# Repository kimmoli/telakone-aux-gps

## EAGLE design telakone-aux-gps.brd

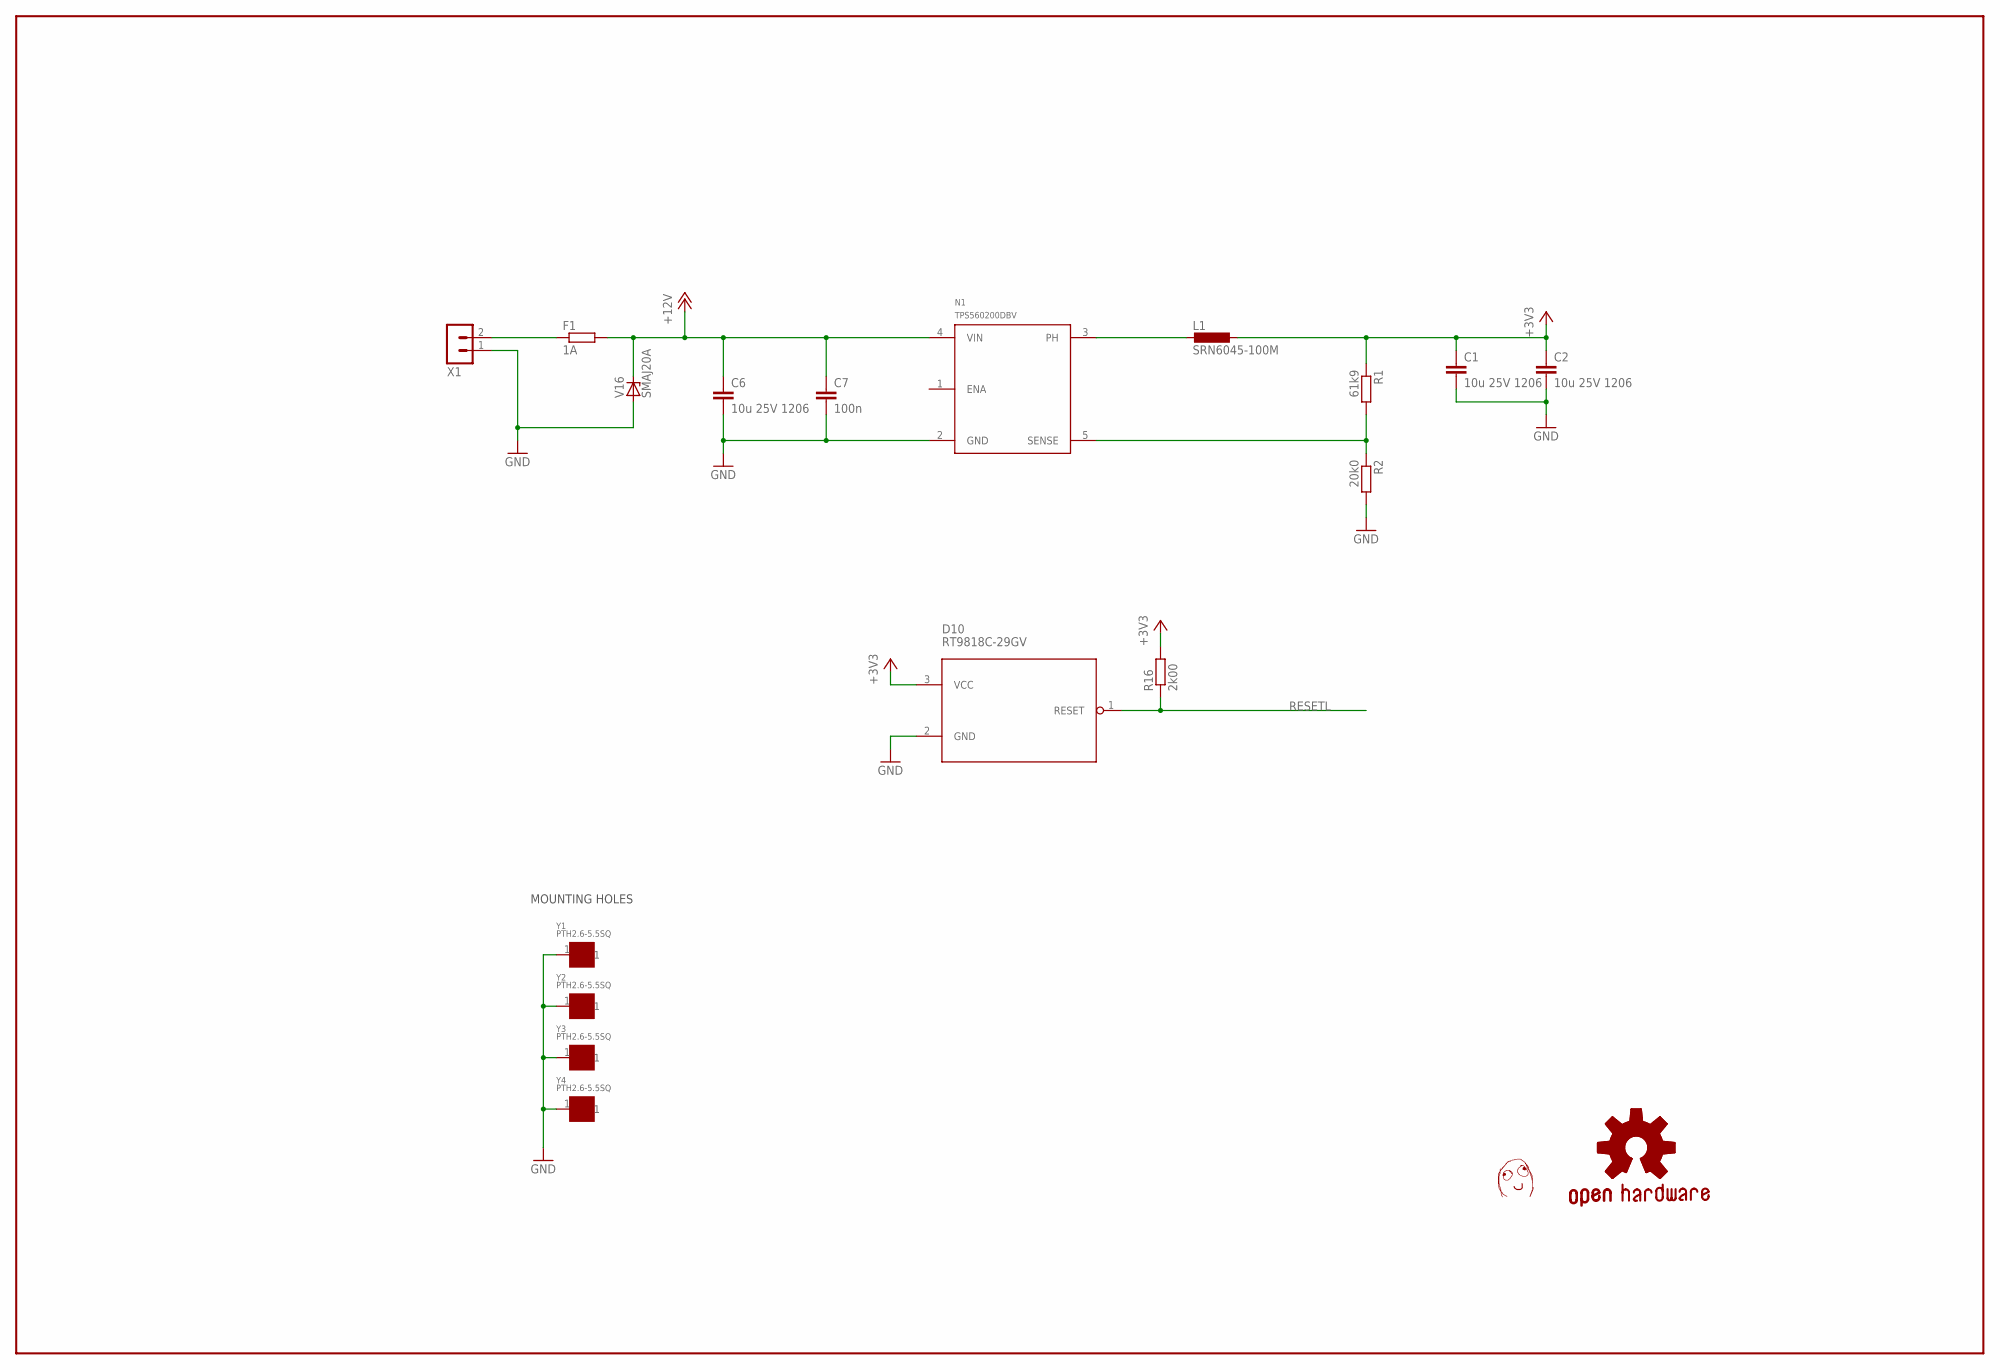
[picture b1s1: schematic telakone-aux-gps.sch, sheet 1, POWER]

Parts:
C1, C2, C6: 10u 25V 1206; C1206
C7: 100n; C0603
D10: RT9818C-29GV; SOT23
F1: 1A; R1206
L1: SRN6045-100M; SRN6045
N1: TPS560200DBV; SOT95P280X145-5N
R1: 61k9; R0603
R2: 20k0; R0603
R16: 2k00; R0603
U$5: DAFUG
V16: SMAJ20A; DO214AC
X1: TE_RUUVILIITIN2
Y1, Y2, Y3, Y4: PTH2.6-5.5SQ; PTH-2.6-5.5SQ

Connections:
+3V3: C1.1, C2.1, D10.3 (VCC), L1.1, R1.1, R16.2; also elsewhere on the board
+12V: C6.1, C7.1, F1.2, N1.4 (VIN), V16.C; also elsewhere on the board
+12V_IN: F1.1, X1.2
GND: C1.2, C2.2, C6.2, C7.2, D10.2 (GND), N1.2 (GND), R2.2, V16.A, X1.1, Y1.1, Y2.1, Y3.1, Y4.1; also elsewhere on the board
N1_PHASE: L1.2, N1.3 (PH)
N1_SENSE: N1.5 (SENSE), R1.2, R2.1
RESETL: D10.1 (RESET), R16.1; also elsewhere on the board

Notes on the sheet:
MOUNTING HOLES

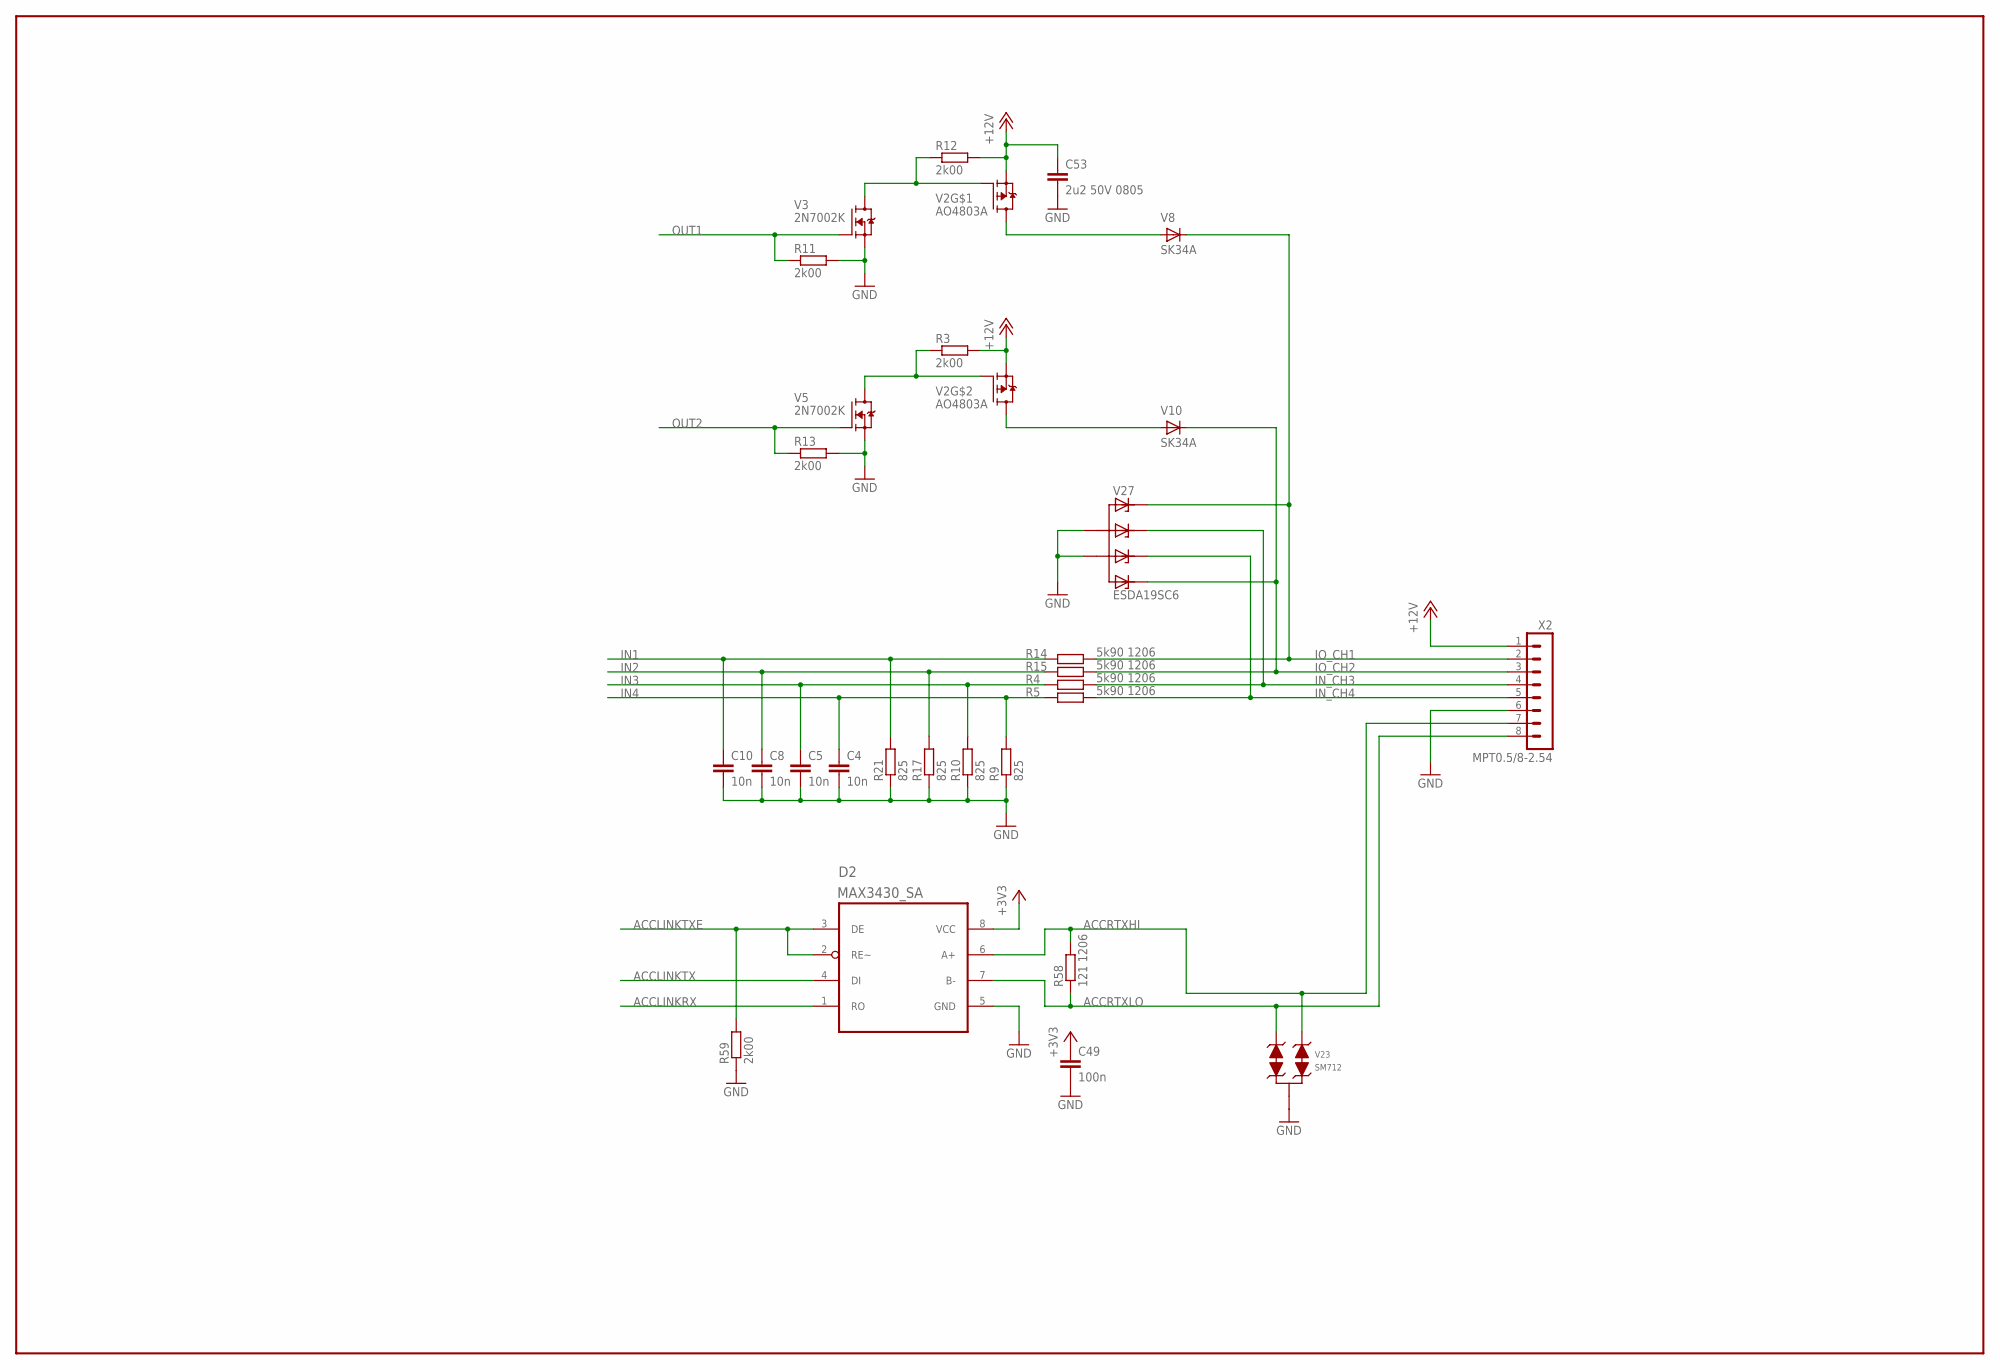
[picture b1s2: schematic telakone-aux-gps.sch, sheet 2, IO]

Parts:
C4, C5, C8, C10: 10n; C0603
C49: 100n; C0603
C53: 2u2 50V 0805; C0805
D2: MAX3430_SA; SOIC8-N_MC
R3, R11, R12, R13, R59: 2k00; R0603
R4, R5, R14, R15: 5k90 1206; R1206
R9, R10, R17, R21: 825; R0603
R58: 121 1206; R1206
V2: AO4803A; SOIC8-N_MC
V3, V5: 2N7002K; SOT23
V8, V10: SK34A; DO214AC
V23: SM712; SOT23
V27: ESDA19SC6; SOT23-6
X2: MPT0.5/8-2.54

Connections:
+3V3: C49.1, D2.8 (VCC); also elsewhere on the board
+12V: C53.1, R3.2, R12.2, V2.1 (S), V2.3 (S), X2.1; also elsewhere on the board
ACCLINKRX: D2.1 (RO); also elsewhere on the board
ACCLINKTX: D2.4 (DI); also elsewhere on the board
ACCLINKTXE: D2.2 (RE~), D2.3 (DE), R59.2; also elsewhere on the board
ACCRTXHI: D2.6 (A+), R58.2, V23.1, X2.7
ACCRTXLO: D2.7 (B-), R58.1, V23.2, X2.8
GND: C4.2, C5.2, C8.2, C10.2, C49.2, C53.2, D2.5 (GND), R9.1, R10.1, R11.2, R13.2, R17.1, R21.1, R59.1, V3.2 (S), V5.2 (S), V23.3, V27.2 (A), V27.5 (A1), X2.6; also elsewhere on the board
IN1: C10.1, R14.1, R21.2; also elsewhere on the board
IN2: C8.1, R15.1, R17.2; also elsewhere on the board
IN3: C5.1, R4.1, R10.2; also elsewhere on the board
IN4: C4.1, R5.1, R9.2; also elsewhere on the board
IN_CH3: R4.2, V27.3 (C1), X2.4
IN_CH4: R5.2, V27.4 (C2), X2.5
IO_CH1: R14.2, V8.C, V27.1 (C), X2.2
IO_CH2: R15.2, V10.C, V27.6 (C3), X2.3
unnamed: R3.1, V2.2 (G), V5.3 (D)
unnamed: R12.1, V2.4 (G), V3.3 (D)
NERT: V2.5 (D), V2.6 (D), V8.A
NERT1: V2.7 (D), V2.8 (D), V10.A
OUT1: R11.1, V3.1 (G); also elsewhere on the board
OUT2: R13.1, V5.1 (G); also elsewhere on the board

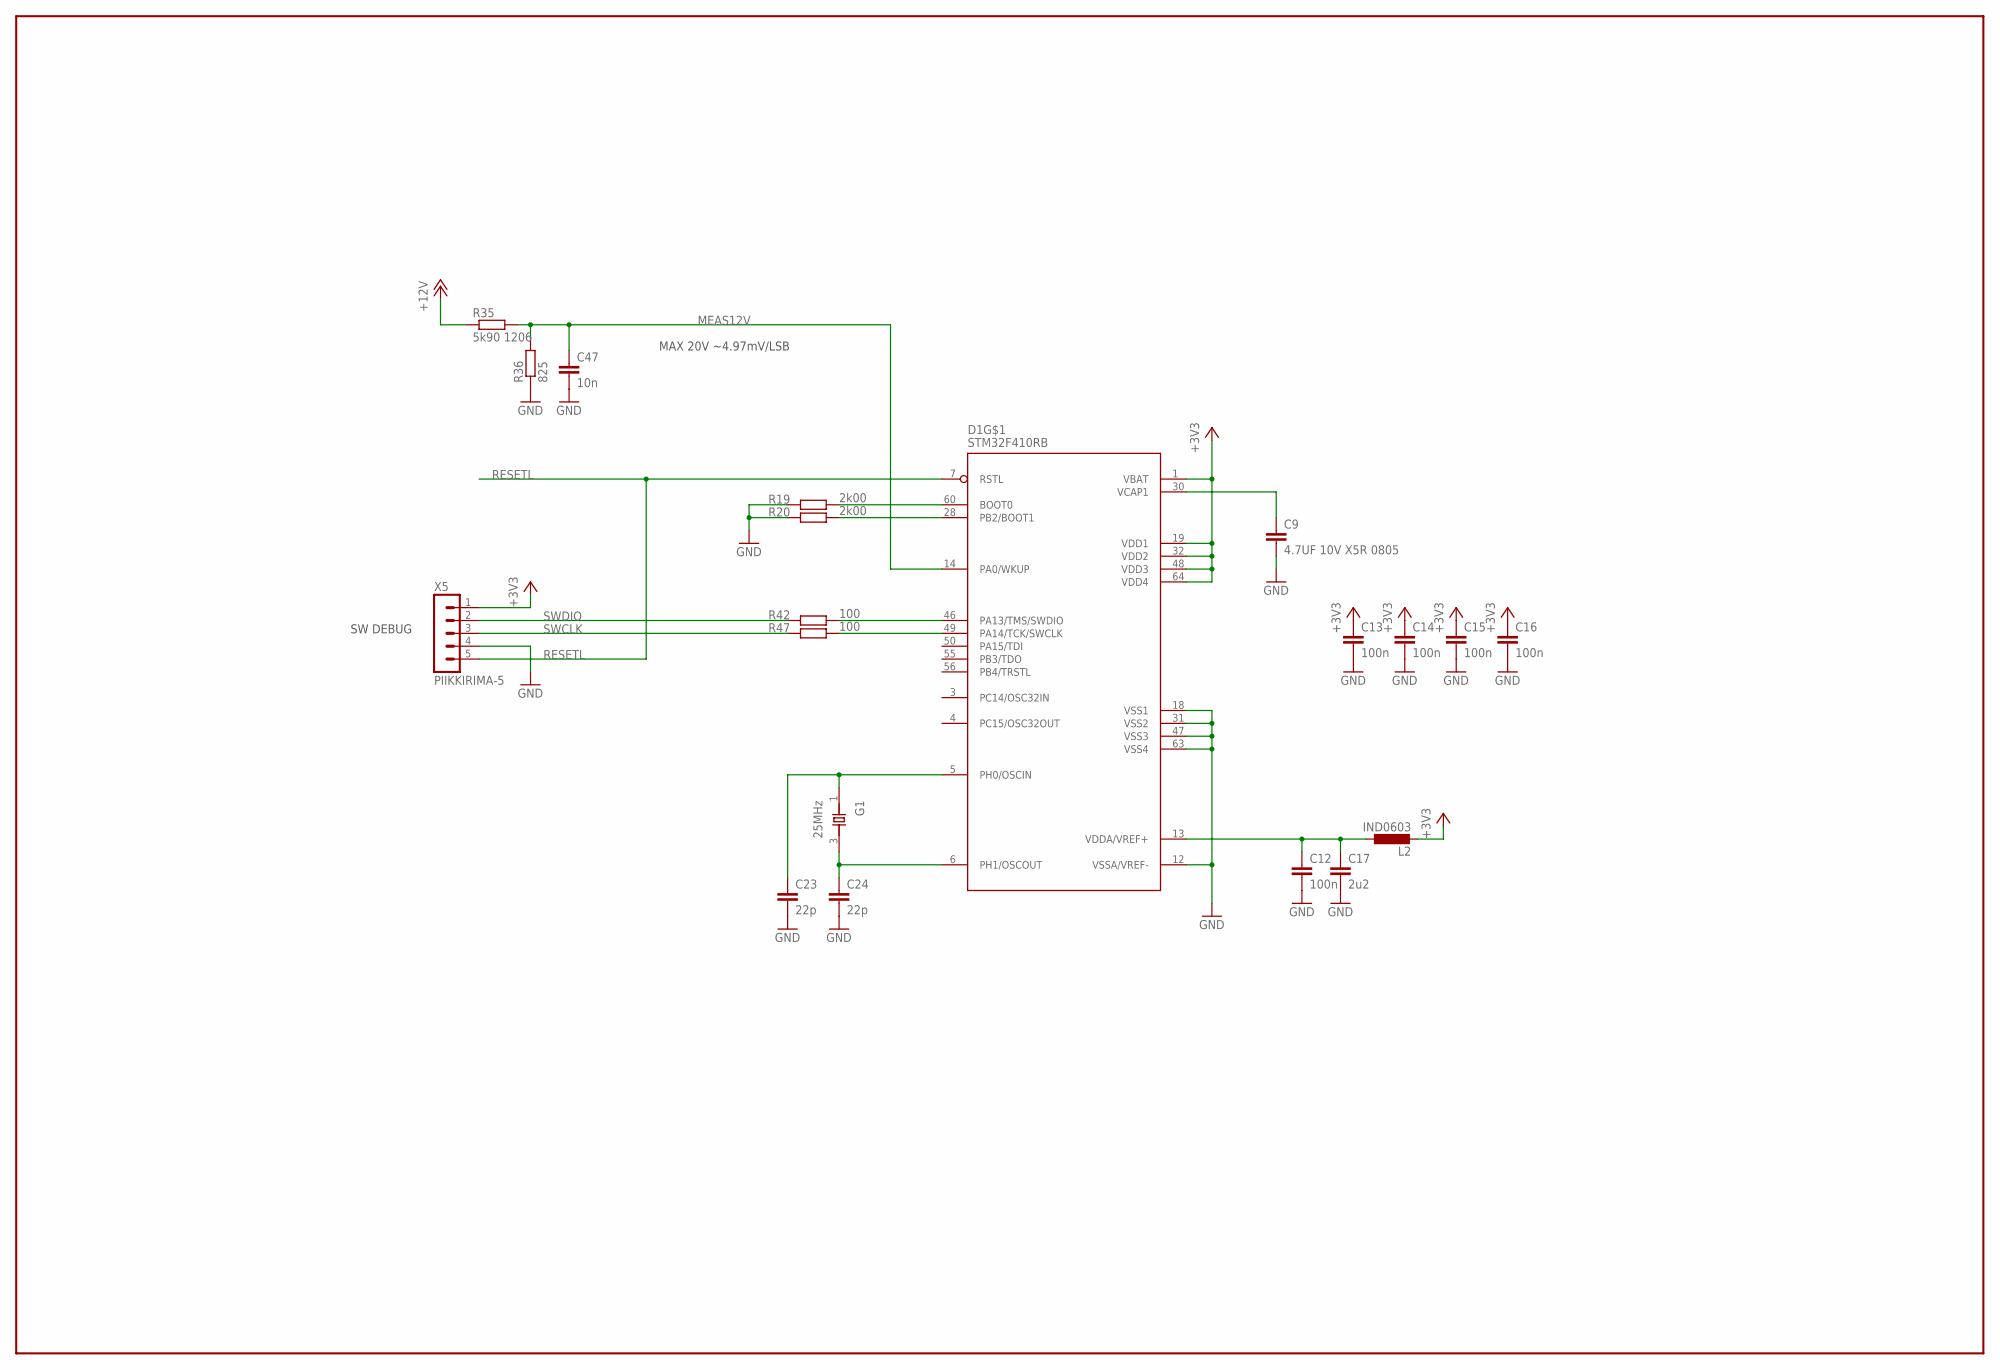
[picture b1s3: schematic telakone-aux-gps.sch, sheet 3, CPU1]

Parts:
C9: 4.7UF 10V X5R 0805; C0805
C12, C13, C14, C15, C16: 100n; C0603
C17: 2u2; C0603
C23, C24: 22p; C0603
C47: 10n; C0603
D1: STM32F410RB; LQFP-64
G1: 25MHz; X_3225
L2: IND0603; R0603
R19, R20: 2k00; R0603
R35: 5k90 1206; R1206
R36: 825; R0603
R42, R47: 100; R0603
X5: PIIKKIRIMA-5

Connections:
+3V3: C13.1, C14.1, C15.1, C16.1, D1.1 (VBAT), D1.19 (VDD1), D1.32 (VDD2), D1.48 (VDD3), D1.64 (VDD4), L2.2, X5.1; also elsewhere on the board
+12V: R35.1; also elsewhere on the board
BOOT0: D1.60 (BOOT0), R19.2
BOOT1: D1.28 (PB2/BOOT1), R20.2
GND: C9.2, C12.2, C13.2, C14.2, C15.2, C16.2, C17.2, C23.2, C24.2, C47.2, D1.12 (VSSA/VREF-), D1.18 (VSS1), D1.31 (VSS2), D1.47 (VSS3), D1.63 (VSS4), R19.1, R20.1, R36.1, X5.4; also elsewhere on the board
MEAS12V: C47.1, D1.14 (PA0/WKUP), R35.2, R36.2
OSCIN: C23.1, D1.5 (PH0/OSCIN), G1.1 (X1)
OSCOUT: C24.1, D1.6 (PH1/OSCOUT), G1.3 (X2)
RESETL: D1.7 (RSTL), X5.5; also elsewhere on the board
SWCLK: R47.1, X5.3
SWCLK_CPU: D1.49 (PA14/TCK/SWCLK), R47.2
SWDIO: R42.1, X5.2
SWDIO_CPU: D1.46 (PA13/TMS/SWDIO), R42.2
VCAP1: C9.1, D1.30 (VCAP1)
VDDA: C12.1, C17.1, D1.13 (VDDA/VREF+), L2.1

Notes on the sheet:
SW DEBUG
MAX 20V ~4.97mV/LSB

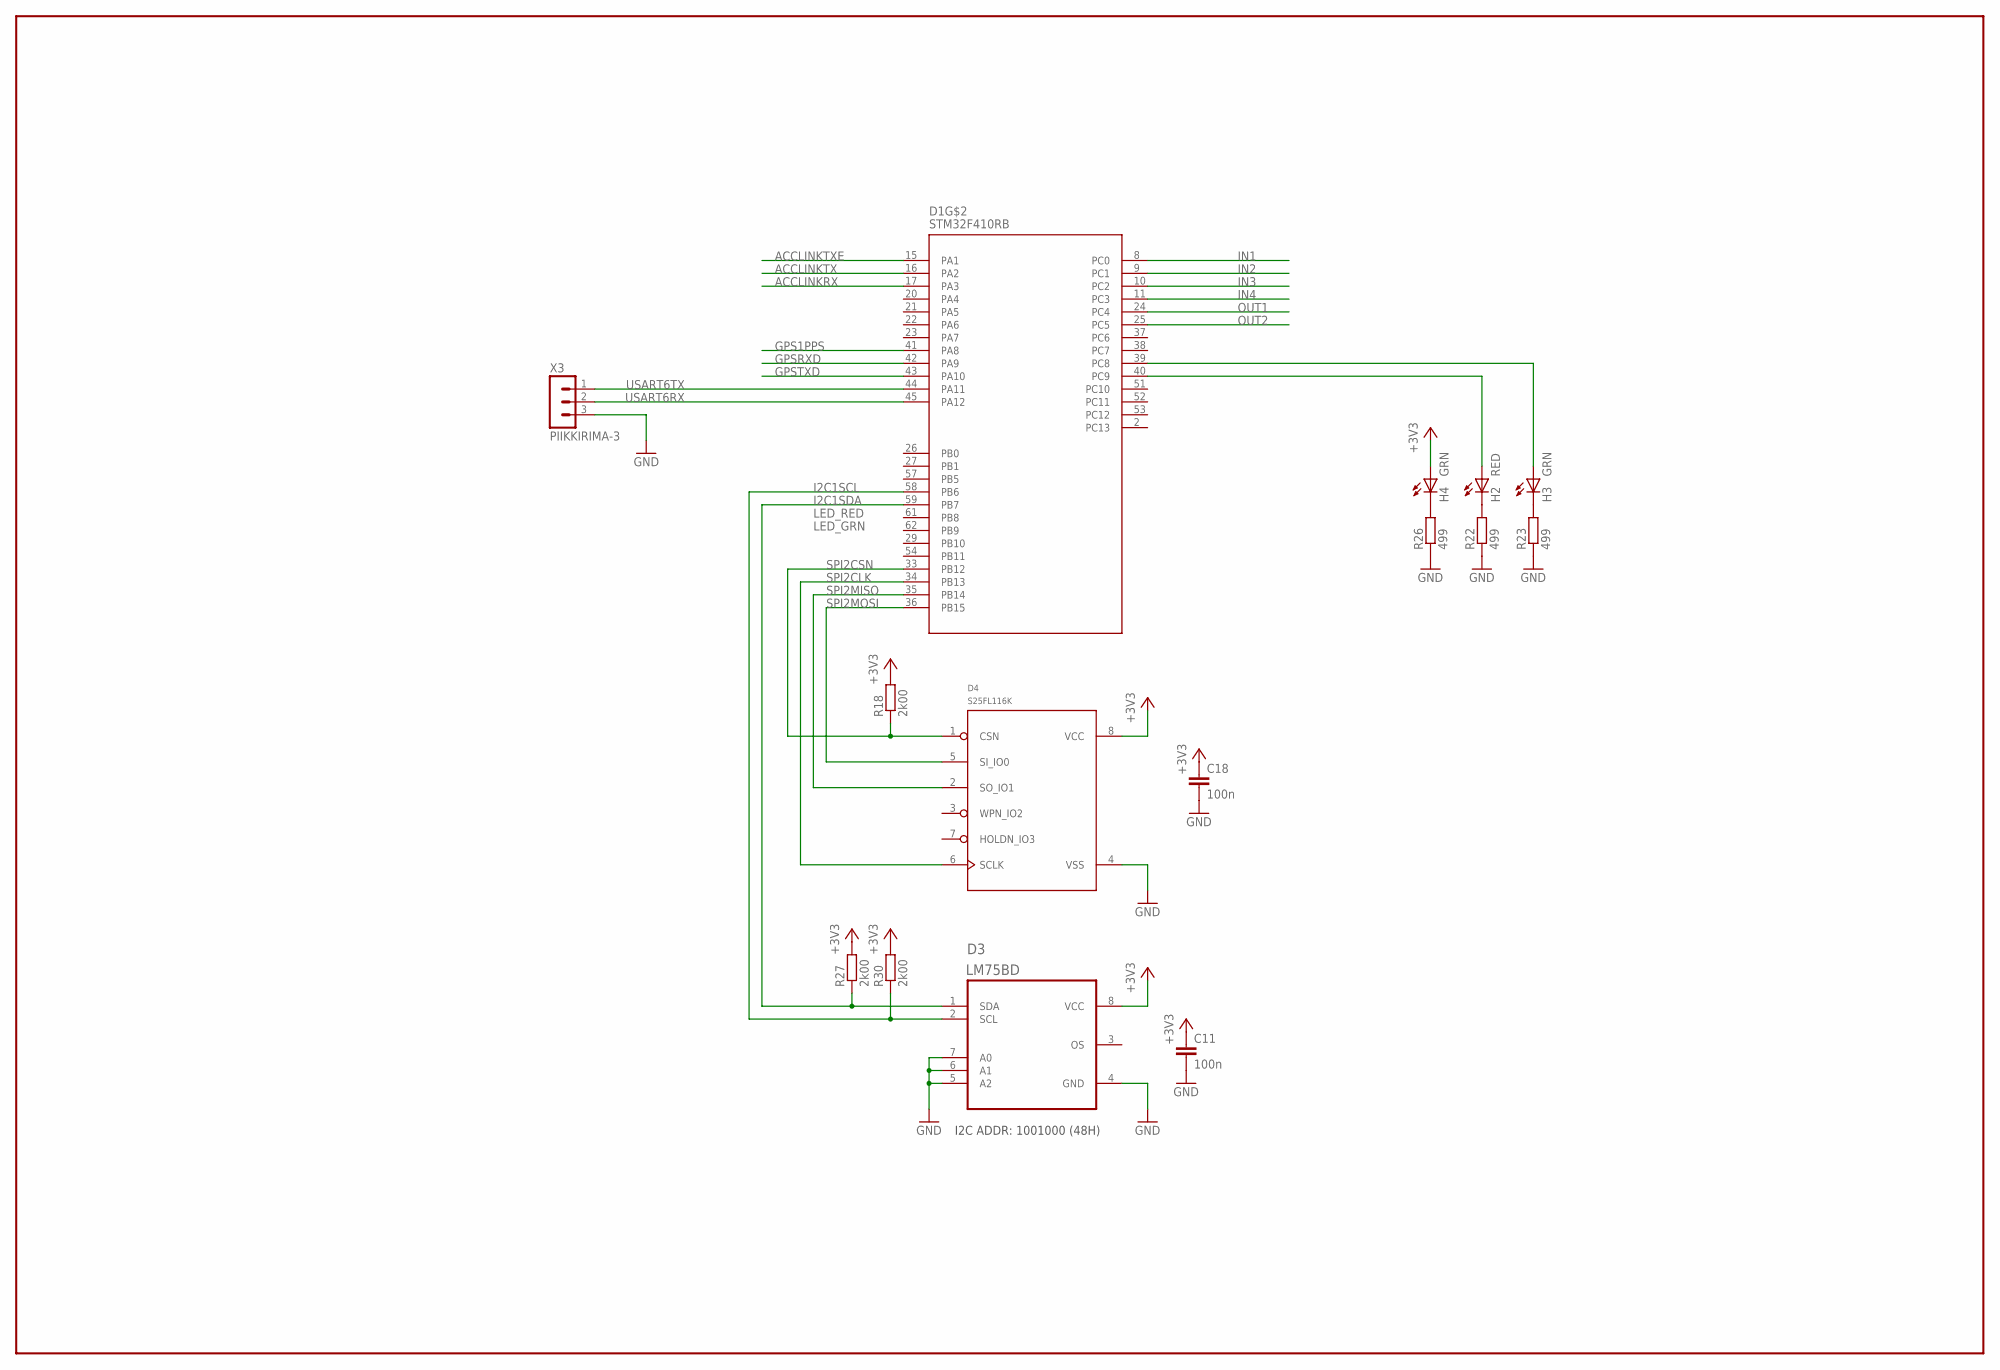
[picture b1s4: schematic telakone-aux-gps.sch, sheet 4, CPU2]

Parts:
C11, C18: 100n; C0603
D1: STM32F410RB; LQFP-64
D3: LM75BD; SOIC8-N_MC
D4: S25FL116K; SOIC8-N_MC
H2: RED; CHIP-LED0603
H3, H4: GRN; CHIP-LED0603
R18, R27, R30: 2k00; R0603
R22, R23, R26: 499; R0603
X3: PIIKKIRIMA-3

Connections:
+3V3: C11.1, C18.1, D3.8 (VCC), D4.8 (VCC), H4.A, R18.2, R27.2, R30.2; also elsewhere on the board
ACCLINKRX: D1.17 (PA3); also elsewhere on the board
ACCLINKTX: D1.16 (PA2); also elsewhere on the board
ACCLINKTXE: D1.15 (PA1); also elsewhere on the board
GND: C11.2, C18.2, D3.4 (GND), D3.5 (A2), D3.6 (A1), D3.7 (A0), D4.4 (VSS), R22.1, R23.1, R26.1, X3.3; also elsewhere on the board
GPS1PPS: D1.41 (PA8); also elsewhere on the board
GPSRXD: D1.42 (PA9); also elsewhere on the board
GPSTXD: D1.43 (PA10); also elsewhere on the board
I2C1SCL: D1.58 (PB6), D3.2 (SCL), R30.1
I2C1SDA: D1.59 (PB7), D3.1 (SDA), R27.1
IN1: D1.8 (PC0); also elsewhere on the board
IN2: D1.9 (PC1); also elsewhere on the board
IN3: D1.10 (PC2); also elsewhere on the board
IN4: D1.11 (PC3); also elsewhere on the board
LED_GRN: D1.39 (PC8), H3.A
LED_RED: D1.40 (PC9), H2.A
unnamed: H3.C, R23.2
unnamed: H2.C, R22.2
unnamed: H4.C, R26.2
OUT1: D1.24 (PC4); also elsewhere on the board
OUT2: D1.25 (PC5); also elsewhere on the board
SPI2CLK: D1.34 (PB13), D4.6 (SCLK)
SPI2CSN: D1.33 (PB12), D4.1 (CSN), R18.1
SPI2MISO: D1.35 (PB14), D4.2 (SO_IO1)
SPI2MOSI: D1.36 (PB15), D4.5 (SI_IO0)
USART6RX: D1.45 (PA12), X3.2
USART6TX: D1.44 (PA11), X3.1

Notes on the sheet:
I2C ADDR: 1001000 (48H)

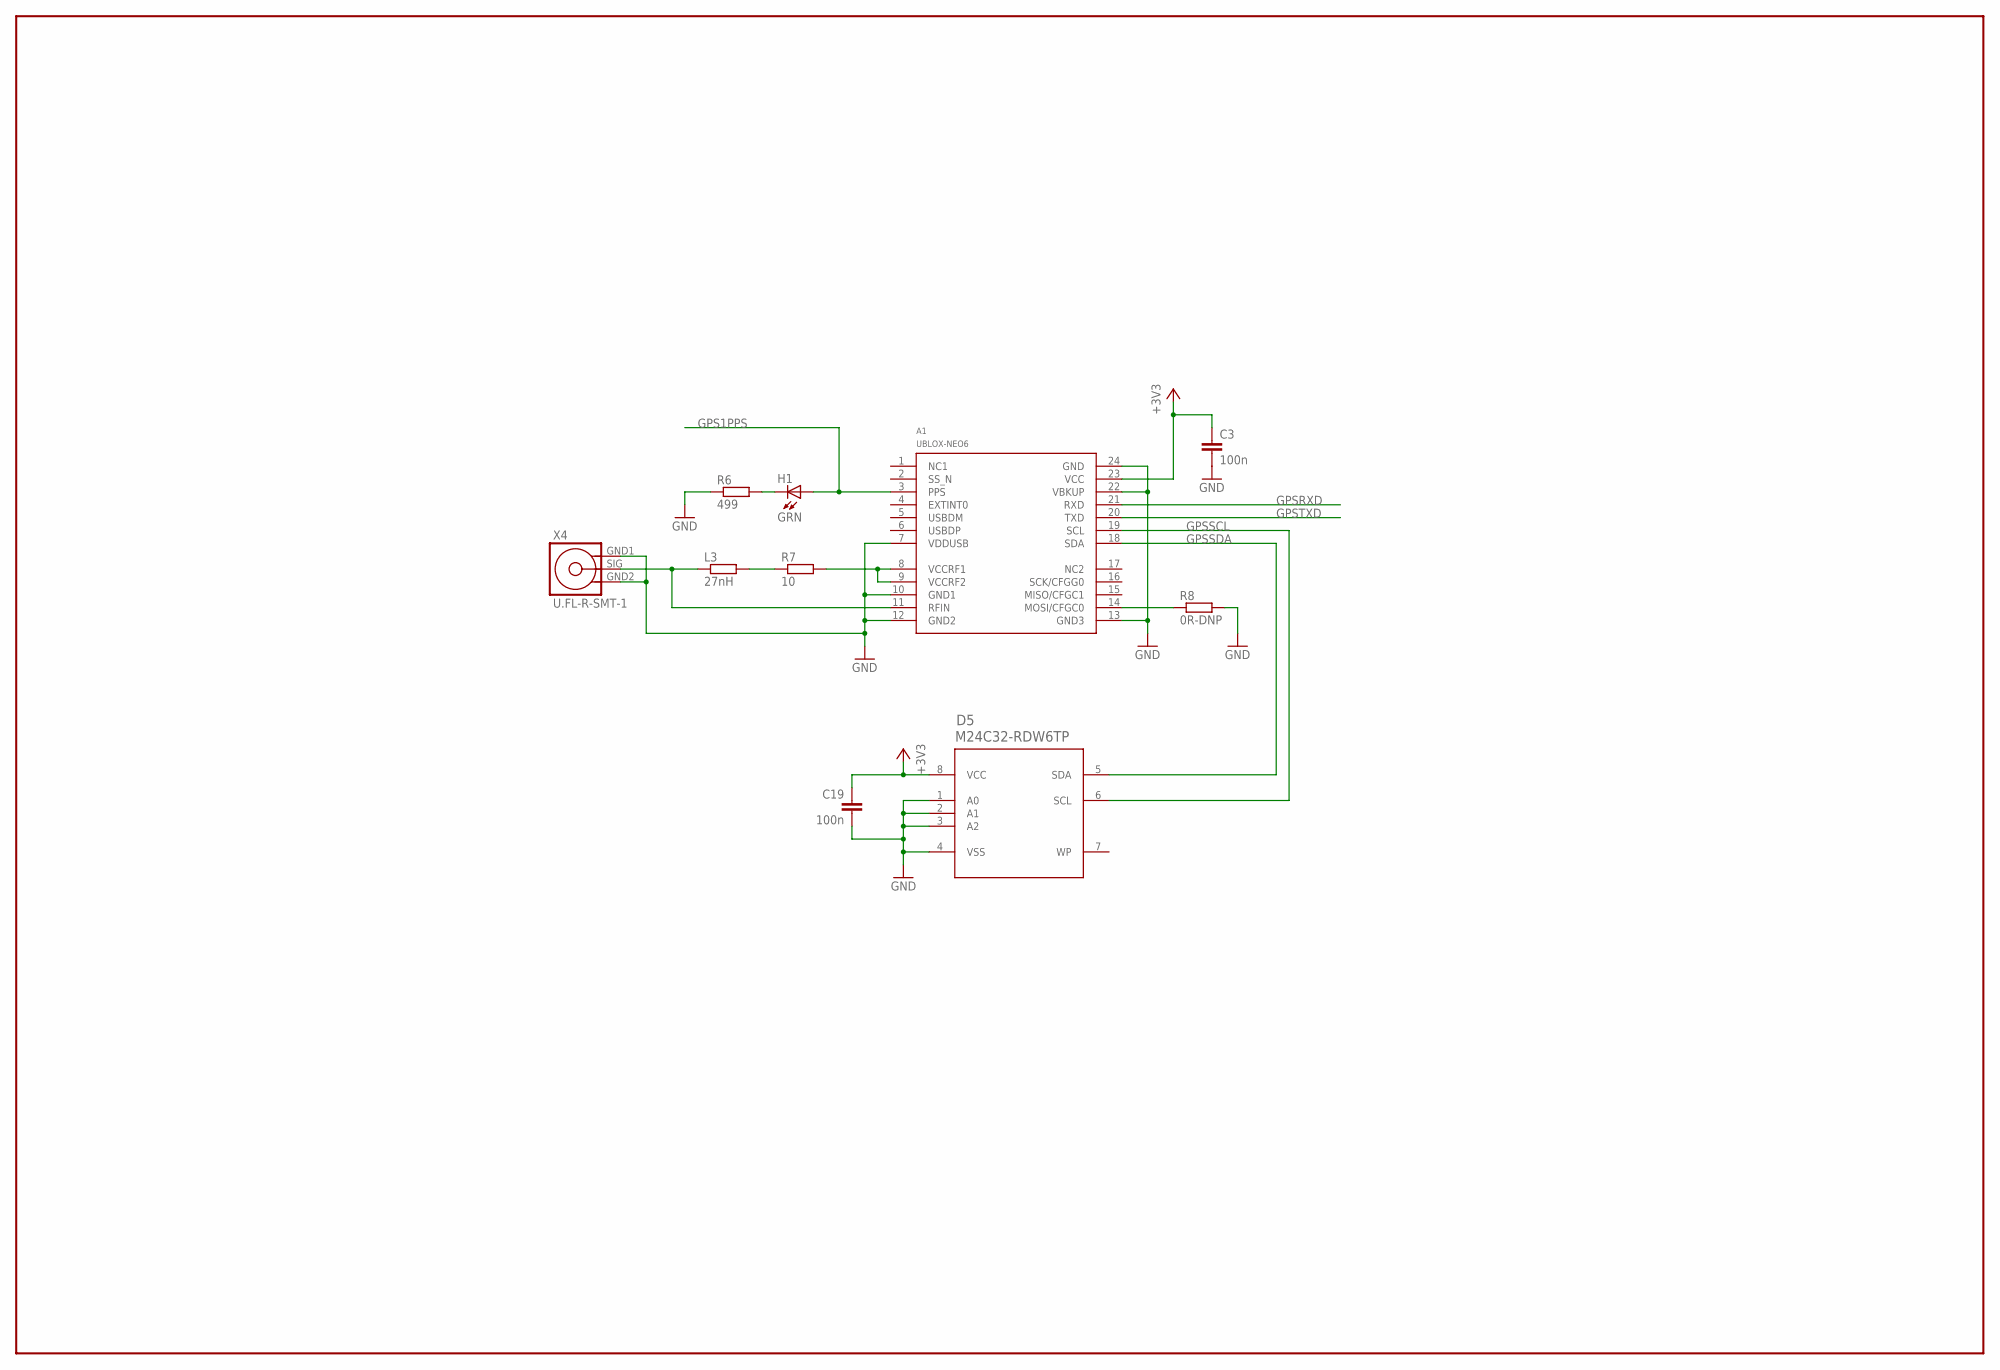
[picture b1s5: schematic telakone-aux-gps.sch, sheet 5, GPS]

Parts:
A1: UBLOX-NEO6
C3, C19: 100n; C0603
D5: M24C32-RDW6TP; TSSOP8-66
H1: GRN; CHIP-LED0603
L3: 27nH; R0603
R6: 499; R0603
R7: 10; R0603
R8: 0R-DNP; R0603
X4: U.FL-R-SMT-1

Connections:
+3V3: A1.23 (VCC), C3.1, C19.1, D5.8 (VCC); also elsewhere on the board
GND: A1.7 (VDDUSB), A1.10 (GND1), A1.12 (GND2), A1.13 (GND3), A1.22 (VBKUP), A1.24 (GND), C3.2, C19.2, D5.1 (A0), D5.2 (A1), D5.3 (A2), D5.4 (VSS), R6.1, R8.2, X4.GND1 (1), X4.GND2 (3); also elsewhere on the board
GPS1PPS: A1.3 (PPS), H1.A; also elsewhere on the board
GPSRF: A1.11 (RFIN), L3.1, X4.SIG (2)
GPSRXD: A1.21 (RXD); also elsewhere on the board
GPSSCL: A1.19 (SCL), D5.6 (SCL)
GPSSDA: A1.18 (SDA), D5.5 (SDA)
GPSTXD: A1.20 (TXD); also elsewhere on the board
unnamed: H1.C, R6.2
unnamed: L3.2, R7.1
unnamed: A1.14 (MOSI/CFGC0), R8.1
VCCRF: A1.8 (VCCRF1), A1.9 (VCCRF2), R7.2

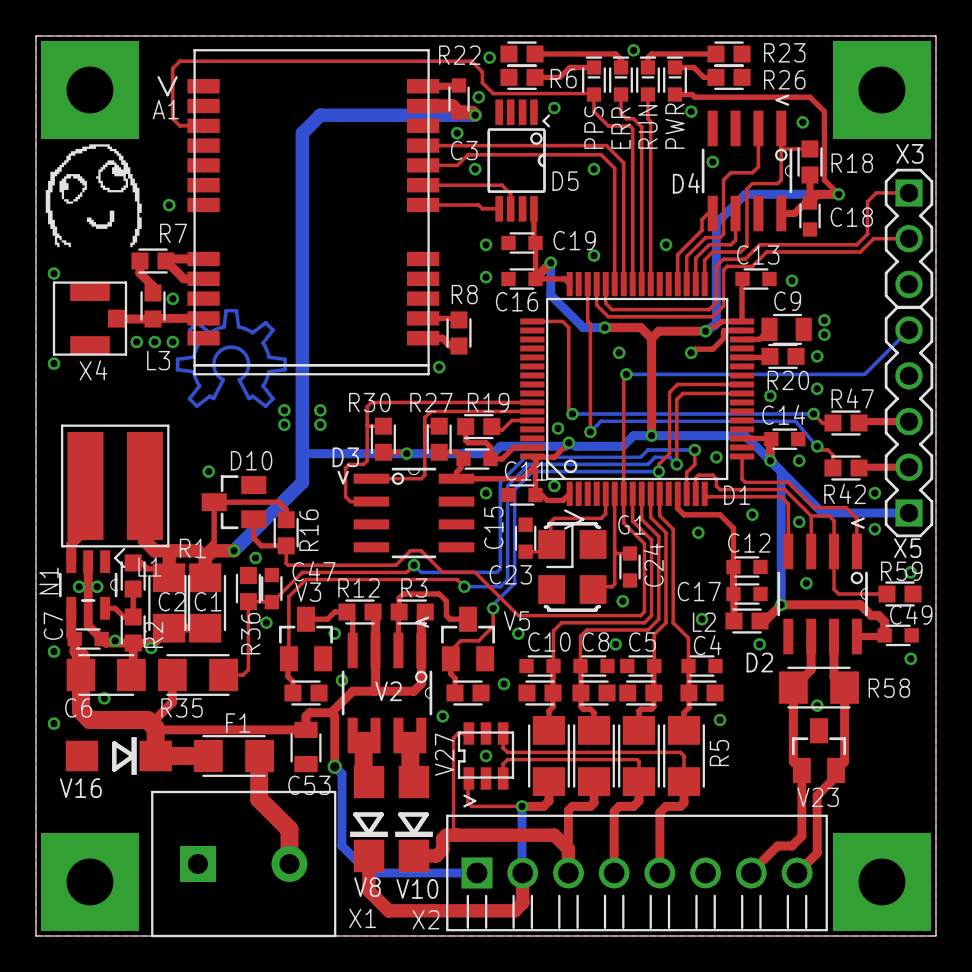
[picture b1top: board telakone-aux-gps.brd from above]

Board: 2 copper layers, 50.0 x 50.0 mm, 92 parts (1 on the bottom side), 60 nets.

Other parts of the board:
U$1: DAFUG

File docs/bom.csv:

"Qty";"Value";"Device";"Package";"Parts";"Description";"";
"1";"";"TE_RUUVILIITIN2";"TE_RUUVILIITIN2";"X1";"";"";
"1";"0R-DNP";"RES0603";"R0603";"R8";"";"";
"1";"10";"RES0603";"R0603";"R7";"";"";
"2";"100";"RES0603";"R0603";"R42, R47";"";"";
"11";"100n";"CAP0603";"C0603";"C3, C7, C11, C12, C13, C14, C15, C16, C18, C19, C49";"";"";
"5";"10n";"CAP0603";"C0603";"C4, C5, C8, C10, C47";"";"";
"3";"10u 25V 1206";"CAP1206";"C1206";"C1, C2, C6";"";"";
"1";"121 1206";"RES1206";"R1206";"R58";"";"";
"1";"1A";"RES1206";"R1206";"F1";"";"";
"1";"20k0";"RES0603";"R0603";"R2";"";"";
"2";"22p";"CAP0603";"C0603";"C23, C24";"";"";
"1";"25MHz";"XTAL_3225_SMD";"X_3225";"G1";"CRYSTAL CLOCK OSCILLATORS";"";
"1";"27nH";"RES0603";"R0603";"L3";"";"";
"2";"2N7002K";"2N7002K";"SOT23";"V3, V5";"";"";
"11";"2k00";"RES0603";"R0603";"R3, R11, R12, R13, R16, R18, R19, R20, R27, R30, R59";"";"";
"1";"2u2";"CAP0603";"C0603";"C17";"";"";
"1";"2u2 50V 0805";"CAP0805";"C0805";"C53";"";"";
"1";"4.7UF 10V X5R 0805";"CAP0805";"C0805";"C9";"";"";
"4";"499";"RES0603";"R0603";"R6, R22, R23, R26";"";"";
"5";"5k90 1206";"RES1206";"R1206";"R4, R5, R14, R15, R35";"";"";
"1";"61k9";"RES0603";"R0603";"R1";"";"";
"5";"825";"RES0603";"R0603";"R9, R10, R17, R21, R36";"";"";
"1";"AO4803A";"AO4803A";"SOIC8-N_MC";"V2";"";"";
"1";"DAFUG";"DAFUG";"DAFUG";"U$5";"";"";
"1";"ESDA19SC6";"ESDAXXSC6";"SOT23-6";"V27";"";"";
"3";"GRN";"LEDCHIP-LED0603";"CHIP-LED0603";"H1, H3, H4";"LED";"";
"1";"IND0603";"IND0603";"R0603";"L2";"";"";
"1";"LM75BD";"LM75BD";"SOIC8-N_MC";"D3";"";"";
"1";"M24C32-RDW6TP";"M24C32-RDW6TP";"TSSOP8-66";"D5";"";"";
"1";"MAX3430_SA";"MAX3088_SA";"SOIC8-N_MC";"D2";"";"";
"1";"MPT0.5/8-2.54";"MPT0.5/8-2.54";"MPT0.5/8-2.54";"X2";"";"";
"1";"PIIKKIRIMA-3";"PIIKKIRIMA-3";"PIIKKIRIMA-3";"X3";"";"";
"1";"PIIKKIRIMA-5";"PIIKKIRIMA-5";"PIIKKIRIMA-5";"X5";"";"";
"4";"PTH2.6-5.5SQ";"PTH2.6-5.5SQ";"PTH-2.6-5.5SQ";"Y1, Y2, Y3, Y4";"";"";
"1";"RED";"LEDCHIP-LED0603";"CHIP-LED0603";"H2";"LED";"";
"1";"RT9818C-29GV";"RT9818C-29GV";"SOT23";"D10";"";"";
"1";"S25FL116K";"S25FL116K";"SOIC8-N_MC";"D4";"";"";
"2";"SK34A";"SK34A";"DO214AC";"V8, V10";"";"";
"1";"SM712";"SM712";"SOT23";"V23";"";"";
"1";"SMAJ20A";"SMAJXXA";"DO214AC";"V16";"";"";
"1";"SRN6045-100M";"SRN6045-100M";"SRN6045";"L1";"";"";
"1";"STM32F410RB";"STM32F410RB";"LQFP-64";"D1";"";"";
"1";"TPS560200DBV";"TPS560200DBV";"SOT95P280X145-5N";"N1";"";"";
"1";"U.FL-R-SMT-1";"U.FL-R-SMT-1";"U.FL-R-SMT-1";"X4";"";"";
"1";"UBLOX-NEO6";"UBLOX-NEO6";"UBLOX-NEO6";"A1";"";"";

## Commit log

2016-11-19 initial schematic
2016-11-19 add schema pdf
2016-11-19 first placement, all on board
2016-11-19 routed
2016-11-19 tuning
2016-11-19 gerbers
2016-11-19 bom and gerber pdf, tuning
2016-11-19 gerber zip, final screenshot
2016-11-20 fix led netname location
